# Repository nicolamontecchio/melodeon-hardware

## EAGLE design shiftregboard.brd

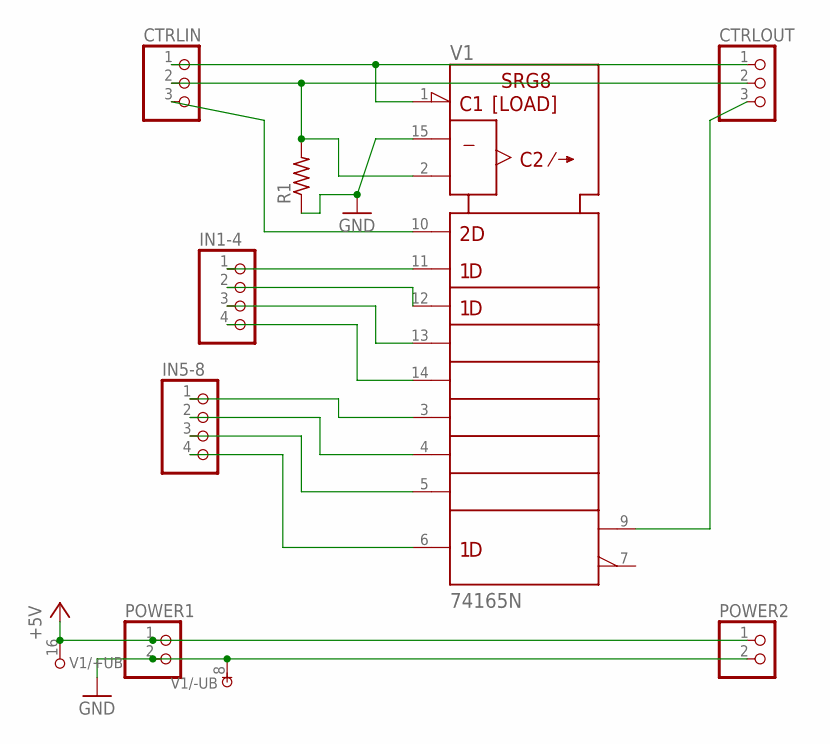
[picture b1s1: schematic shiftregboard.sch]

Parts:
CTRLIN: PINHD-1X3; 1X03
CTRLOUT: PINHD-1X3; 1X03
IN1-4, IN5-8: PINHD-1X4; 1X04
POWER1, POWER2: PINHD-1X2; 1X02
R1: R-US_0207/15; 0207/15
V1: 74165N; DIL16

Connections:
+5V: POWER1.1, POWER2.1, V1.16 (+UB)
GND: POWER1.2, POWER2.2, R1.1, V1.8 (-UB), V1.15 (CLK_INH)
unnamed: CTRLIN.2, CTRLOUT.2, R1.2, V1.2 (CLK)
unnamed: IN1-4.1, V1.11 (A)
unnamed: IN1-4.2, V1.12 (B)
unnamed: IN1-4.3, V1.13 (C)
unnamed: IN1-4.4, V1.14 (D)
unnamed: IN5-8.1, V1.3 (E)
unnamed: IN5-8.2, V1.4 (F)
unnamed: IN5-8.3, V1.5 (G)
unnamed: IN5-8.4, V1.6 (H)
unnamed: CTRLIN.3, V1.10 (SER)
unnamed: CTRLOUT.3, V1.9 (QH)
unnamed: CTRLIN.1, CTRLOUT.1, V1.1 (SH/!LD)

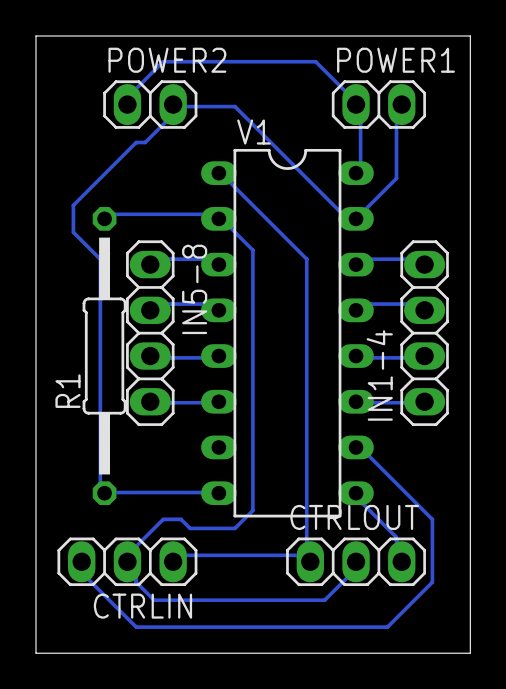
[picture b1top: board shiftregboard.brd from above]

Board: 2 copper layers, 24.1 x 34.3 mm, 8 parts (0 on the bottom side), 14 nets.

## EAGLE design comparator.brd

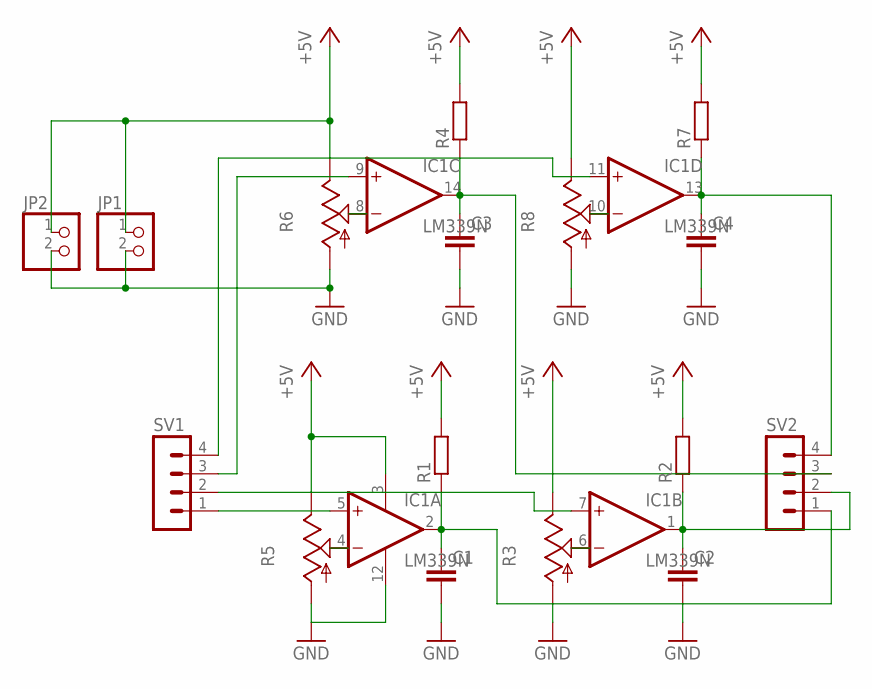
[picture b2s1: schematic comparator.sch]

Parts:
C1, C2, C3, C4: C-EU075-032X103; C075-032X103
IC1: LM339N; DIL14
JP1, JP2: PINHD-1X2; 1X02
R1, R2, R4, R7: R0207/10; 0207/10
R3, R5, R6, R8: TRIM_US-RS3; RS3
SV1, SV2: MA04-1

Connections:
+5V: IC1.3 (V+), JP1.1, JP2.1, R1.2, R2.2, R3.E, R4.2, R5.E, R6.E, R7.2, R8.E
GND: C1.2, C2.2, C3.2, C4.2, IC1.12 (GND), JP1.2, JP2.2, R3.A, R5.A, R6.A, R8.A
unnamed: C1.1, IC1.2 (OUT), R1.1, SV2.1
unnamed: IC1.5 (+IN), SV1.1
unnamed: C2.1, IC1.1 (OUT), R2.1, SV2.2
unnamed: IC1.6 (-IN), R3.S
unnamed: IC1.4 (-IN), R5.S
unnamed: IC1.7 (+IN), SV1.2
unnamed: C3.1, IC1.14 (OUT), R4.1, SV2.3
unnamed: IC1.8 (-IN), R6.S
unnamed: IC1.9 (+IN), SV1.3
unnamed: C4.1, IC1.13 (OUT), R7.1, SV2.4
unnamed: IC1.10 (-IN), R8.S
unnamed: IC1.11 (+IN), SV1.4

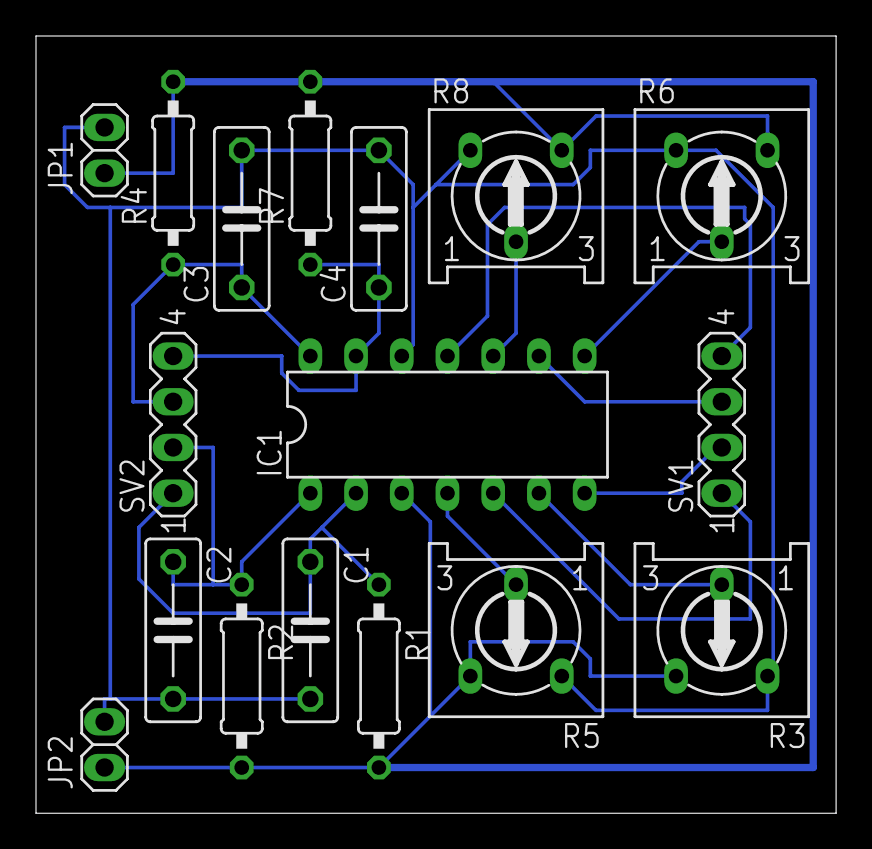
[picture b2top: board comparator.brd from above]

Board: 2 copper layers, 44.5 x 43.2 mm, 17 parts (0 on the bottom side), 14 nets.

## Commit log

2016-01-09 updated arduino code to output midi
2016-01-15 cleanup C code
2016-01-17 i is not 1
2016-01-20 microseconds delays
2016-01-21 epic programming fail bugfix
2016-01-21 use a define
2016-03-24 pages
2016-04-25 github pages
2016-04-25 uppercase
